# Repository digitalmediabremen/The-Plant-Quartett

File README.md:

## The Plant Quartett

2021-2022
printed circuit boards, speaker membranes and metal stands

The Plant Quartet is a sound installation that provides an ambient listening experience of plants by using multiple Soniplasts, a custom-designed instrument that translates biodata from plants into sound. Similar as Chloroplasts, which are organelles that conduct photosynthesis in plants, a Soniplast takes bioelectric potential data from a plant and translates it to sound by using the signal to modulate a simple sine wave.

The installation puts plants at the centre of the focus: they react to the environment but in a slow and subtle manner, which is very different from the time scale and ways of perception of animals/human. The project pays attention to the relative differences in rhythmic cycles among plants and how they contribute together to a musical composition. By amplifying the ubiquitous existence of plants through sound, the objective of the project is to encourage an intimate relationship with plants in a slow, subtle and collective manner.

"Learn about a pine tree from a pine tree, and about a bamboo stalk from a bamboo stalk." - Basho

### Artist Bio
Qianxun Chen is a media artist and researcher. She works at the intersection of art, technology and language, with a focus on generative poetics, the aesthetics of algorithm and digital textuality. Her works tend to bring up artistic and non-human perspectives of the world through alternative usage of technology.

Qianxun Chen was born in 1993 in Beijing and lives and works in Bremen.

### Sound Samples
[Sound Cloud](https://soundcloud.com/user-523089589/the-plant-quatett)

### Links
[PCB Design](https://github.com/digitalmediabremen/plantSonification/blob/main/pcb/pcbDesign.md) |
[Concept](https://github.com/digitalmediabremen/plantSonification/blob/main/concept.md) | [Notes](https://github.com/digitalmediabremen/plantSonification/blob/main/notes.md)

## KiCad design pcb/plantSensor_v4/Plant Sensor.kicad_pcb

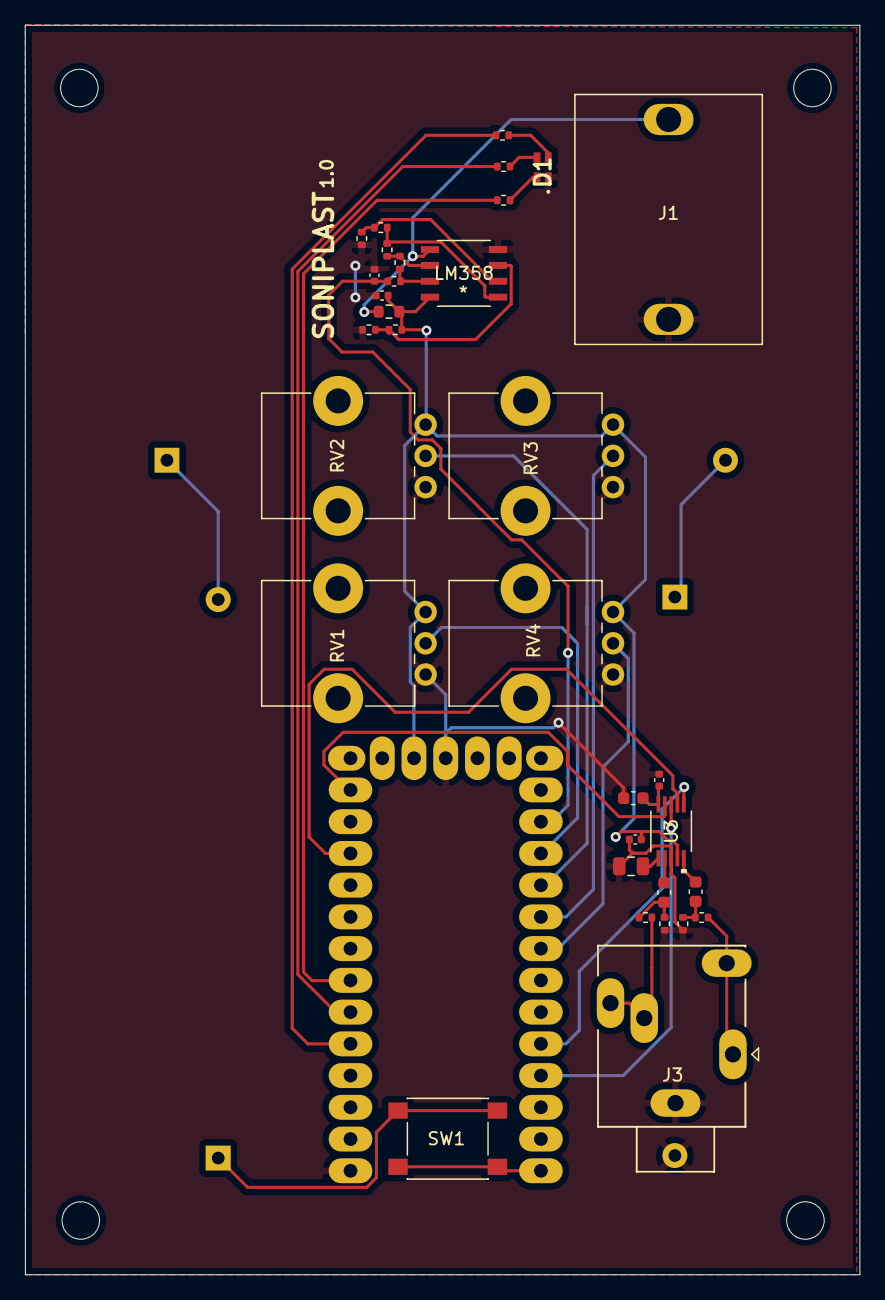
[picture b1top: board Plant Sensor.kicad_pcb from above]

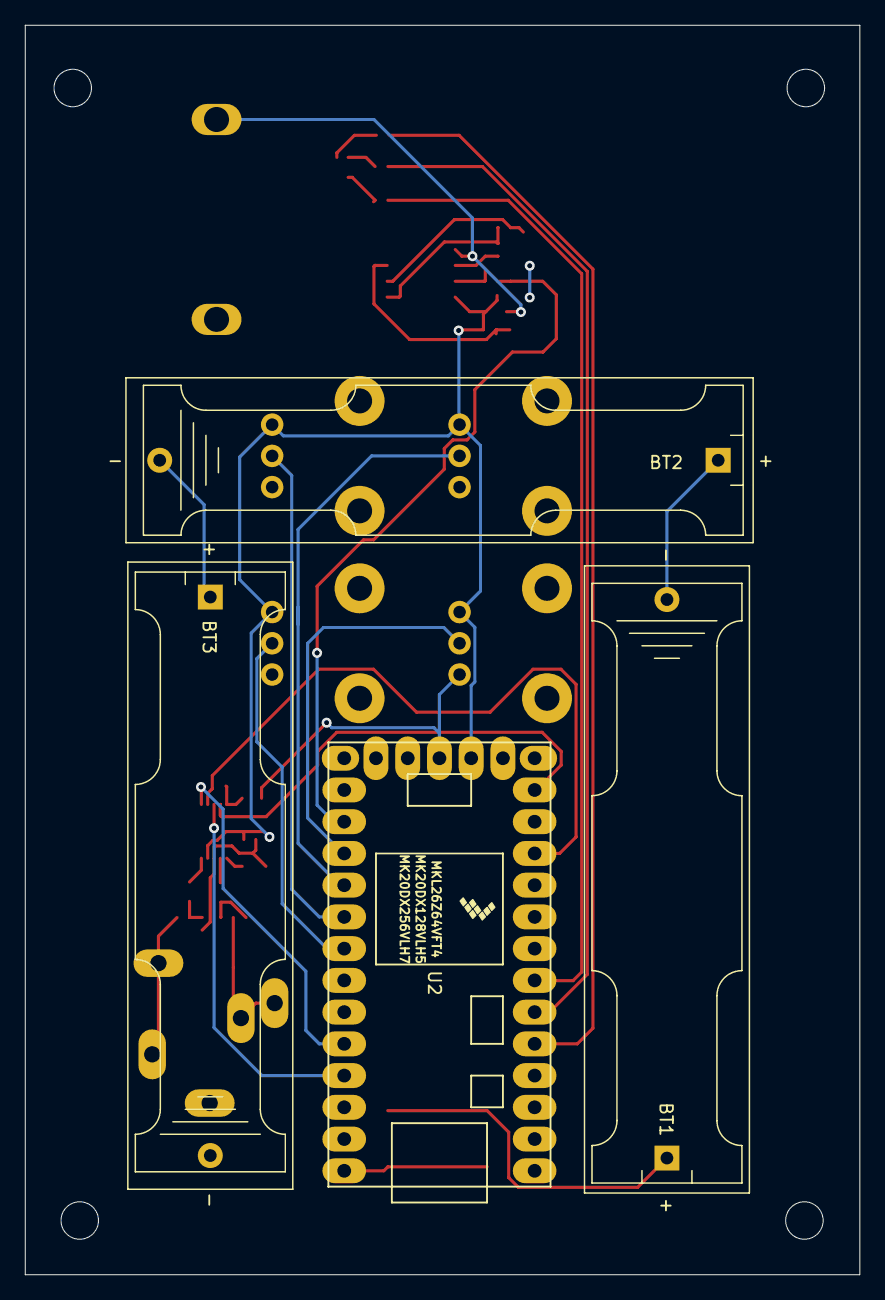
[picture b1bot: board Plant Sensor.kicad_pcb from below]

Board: 2 copper layers, 66.8 x 100.0 mm, 41 parts (4 on the bottom side), 35 nets.

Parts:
BT1, BT2, BT3: Battery_Cell; BatteryHolder_Keystone_2466_1xAAA
C1: 4.7uF; C_0402_1005Metric
C2: 1uF; C_0402_1005Metric
C3, C8: 0.1uF; C_0402_1005Metric
C4, C5, C6: 3,3uF; C_0603_1608Metric
C7: 10uF; C_0805_2012Metric
D1: CLV1L-FKB; 19037ARSGHBHW1S032T
H1, H2, H3, H4: MountingHole; MountingHole_3mm
J1: Sensor Input; HILABEE TS Mono Jack
J3: AudioJack; Jack_3.5mm_Ledino_KB3SPRS_Horizontal
R1: 3.3M; R_0603_1608Metric
R2, R3: 680K; R_0402_1005Metric
R4, R5, R6, R7: 100K; R_0402_1005Metric
R8: 4.7K; R_0402_1005Metric
R9, R10: 10k; R_0402_1005Metric
R11, R12: 470R; R_0402_1005Metric
R13, R14, R15: 220R; R_0402_1005Metric
RV1, RV2, RV3, RV4: R_POT_US; Potentiometer_Alps_RK09K_Single_Vertical
SW1: SW_Push; SW_Push_1P1T_NO_6x6mm_H9.5mm
U1: LM358; LM358DR2G
U2: Teensy3.2; Teensy30_31_32_LC_LargeHoles
U3: CS4344-CZZR

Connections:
/AOUTL: C5.1, U3.7
/AOUTR: C4.1, U3.10
/B: R15.2, U2.7
/G: R14.2, U2.6
/I2S_TX: U2.29, U3.1
/LRCK: U2.30, U3.3
/MCLK: U2.13, U3.4
/R: R13.2, U2.5
/SCLK: U2.11, U3.2
/VIN: SW1.1, U2.33
GND: BT3.2, C1.2, C2.2, C3.2, C6.2, C7.2, C8.2, D1.1, J1.S, J3.G, R3.2, R4.2, R9.1, R10.2, RV1.3, RV2.3, RV3.3, RV4.3, U1.4, U2.1, U2.17, U3.8
unnamed: BT1.1, SW1.2
unnamed: BT1.2, BT2.1
unnamed: BT2.2, BT3.1
unnamed: C4.2, R9.2, R11.2
unnamed: C5.2, R10.1, R12.2
unnamed: C6.1, C8.1, U3.5
unnamed: C7.1, U3.6
unnamed: D1.2, R13.1
unnamed: D1.3, R14.1
unnamed: D1.4, R15.1
unnamed: J1.T, R1.2, U1.5
unnamed: J3.S1, J3.SN1, R12.1
unnamed: J3.T1, J3.TN1, R11.1
unnamed: R2.2, R3.1, U1.3
unnamed: R4.1, R5.2, U1.2
unnamed: R5.1, R6.2, U1.1
unnamed: R6.1, R7.2, U1.6
unnamed: R7.1, R8.2, U1.7
SIGNAL: C1.1, R8.1, U2.22
VCC: C2.1, C3.1, R1.1, R2.1, RV1.1, RV2.1, RV3.1, RV4.1, U1.8, U2.16, U3.9
pot1: RV1.2, U2.23
pot2: RV2.2, U2.24
pot3: RV3.2, U2.25
pot4: RV4.2, U2.26

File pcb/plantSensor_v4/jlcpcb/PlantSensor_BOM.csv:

Comment,Designator,Footprint,JLCPCB Part #
4.7uF Polarized capacitor,C1,C_0402_1005Metric,C23733
1uF Polarized capacitor,C2,C_0402_1005Metric, C52923
"0.1uF Unpolarized capacitor, small symbol","C3,C8",C_0402_1005Metric, C1525
"3,3uF Polarized capacitor","C6,C4,C5",C_0603_1608Metric,C51412
10uF Polarized capacitor,C7,C_0805_2012Metric,C15850
CLV1L-FKB Cree PLCC4 3 in 1 SMD LED,D1,19037ARSGHBHW1S032T,C282128
3.3M Resistor,R1,R_0603_1608Metric,C141659
680K Resistor,"R3,R2",R_0402_1005Metric,C163456
100K Resistor,"R4,R6,R7,R5",R_0402_1005Metric,C144809
4.7K Resistor,R8,R_0402_1005Metric,C140158
10k Resistor,"R10,R9",R_0402_1005Metric, C144807
470R Resistor,"R11,R12",R_0402_1005Metric, C163829
220R Resistor,"R13,R14,R15",R_0402_1005Metric, C25091
"R_POT_US Potentiometer, US symbol","RV1,RV2,RV3,RV4",Potentiometer_Alps_RK09K_Single_Vertical,C209779
"SW_Push Push button switch, generic, two pins",SW1,SW_Push_1P1T_NO_6x6mm_H9.5mm,C273520
"LM358 Dual Operational Amplifiers, DIP-8/SOIC-8/TSSOP-8/VSSOP-8",U1,LM358DR2G,C7950
CS4344-CZZR ,U3,CS4344-CZZR,C8952

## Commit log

2021-01-12 foxdot
2021-01-20 signal commit
2021-01-20 tidy up and sc study files
2021-01-24 more process
2021-01-24 sound samples
2021-01-27 progress
2021-02-01 trio circuit
2021-02-01 24 hours data
2021-02-15 tidy up
2021-02-15 remove log
2021-02-15 format
2021-02-15 add image
2021-02-15 resize
2021-03-06 push
2021-03-07 add mqtt
2021-10-22 update pcb
2021-10-22 minor tweak
2021-11-13 update teensey code
2022-01-30 tidy up md
2022-01-30 add photos
2022-02-03 images optimization
2022-02-03 better links
2022-02-07 update photos
2022-02-07 update photo
2022-02-07 update pcb image
2022-05-09 add speakers research
2022-05-11 more
2022-06-03 add case design file
2022-07-19 add more design files
2022-07-21 back up savvy file
2022-07-21 finalize savvy
2022-10-25 add support structures

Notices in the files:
parts and their libraries:
Copyright 2021 Accelerated Designs. All rights reserved.
